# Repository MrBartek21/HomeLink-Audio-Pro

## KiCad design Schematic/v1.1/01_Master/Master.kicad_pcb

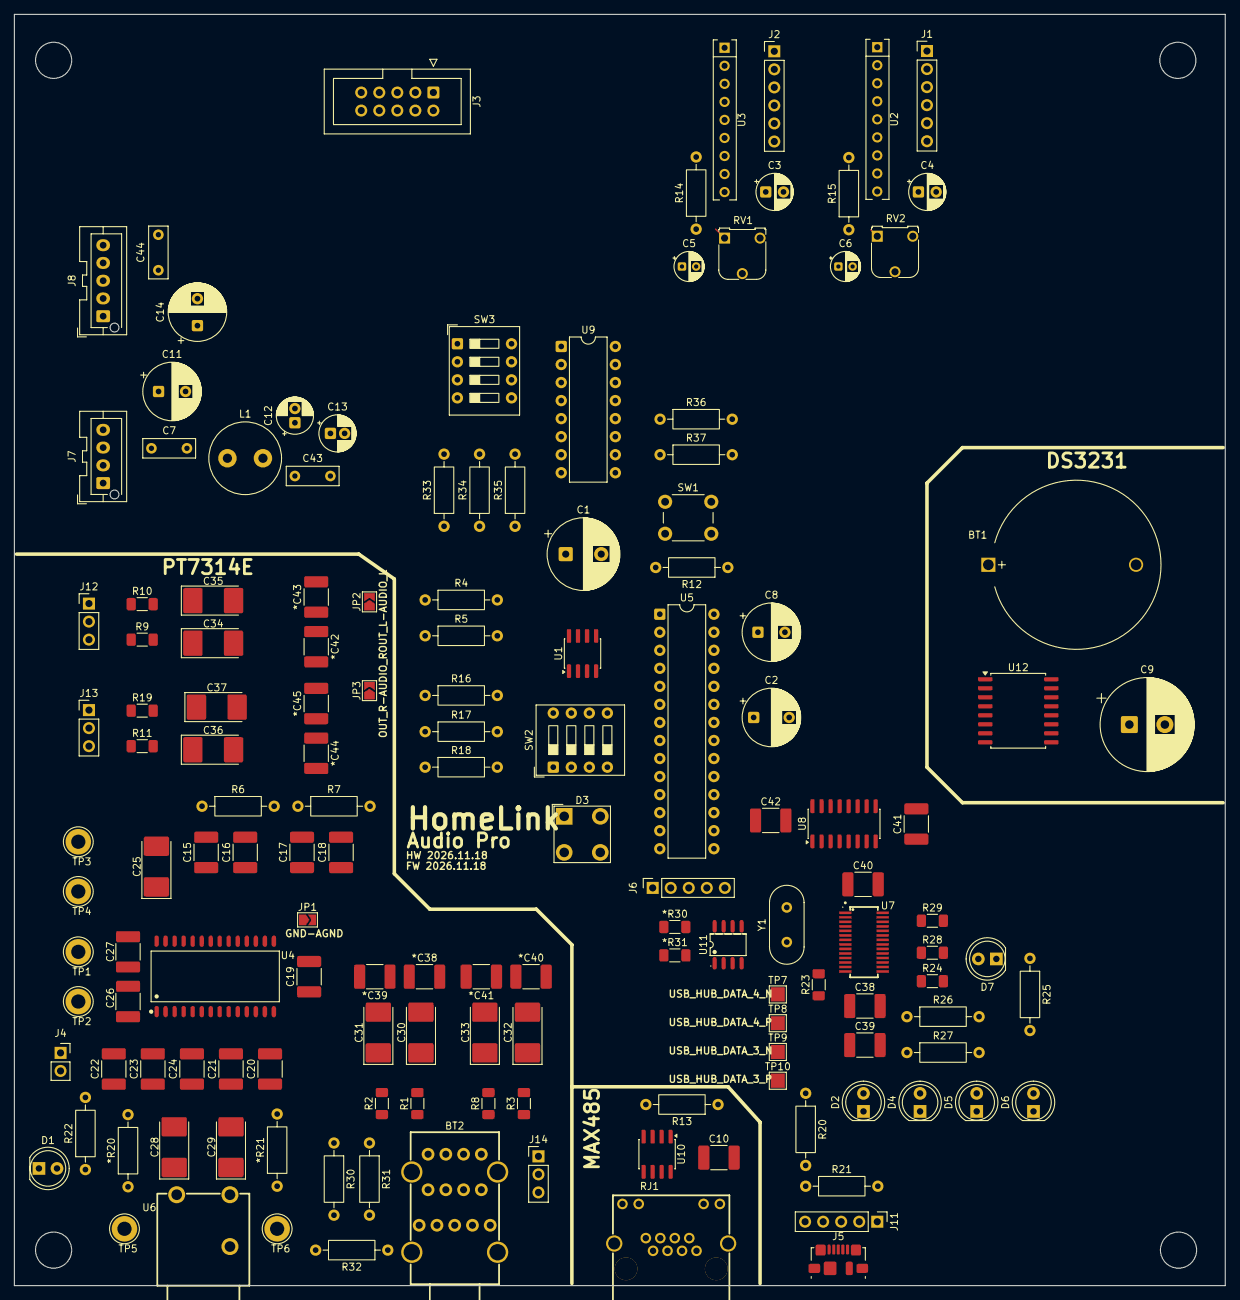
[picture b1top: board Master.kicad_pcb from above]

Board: 2 copper layers, 170.5 x 179.0 mm, 147 parts (0 on the bottom side), 125 nets.

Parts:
*C38, *C39, *C40, *C41, *C42, *C43, *C44, *C45: 470pF; C_1812_4532Metric_Pad1.57x3.40mm_HandSolder
*R20, *R21: 75K; R_Axial_DIN0207_L6.3mm_D2.5mm_P10.16mm_Horizontal
*R30, *R31: 5.1K; R_1206_3216Metric_Pad1.30x1.75mm_HandSolder
BT1: Battery; BatteryHolder_MYOUNG_BS-07-A1BJ001_CR2032
BT2: ABA-JAK-027-K11; AUDIO-TH_ABA-JAK-027-K11
C1: 6.3v 3300uF; CP_Radial_D10.0mm_P5.00mm
C2: 6.3V 1800uF; CP_Radial_D8.0mm_P5.00mm
C3, C4: 16V 10uF; CP_Radial_D5.0mm_P2.50mm
C5, C6: 16V 2.2uF; CP_Radial_D4.0mm_P2.00mm
C7, C43, C44: 100nF 100V; C_Rect_L7.2mm_W2.5mm_P5.00mm
C8: 6.3V 220uF; CP_Radial_D8.0mm_P3.80mm
C9: 35v 1000uF; CP_Radial_D13.0mm_P5.00mm
C10, C15, C16, C17, C18, C20, C21, C26, C39, C40, C41, C42: 100nF; C_1812_4532Metric_Pad1.57x3.40mm_HandSolder
C11, C14: 10V 1000uF; CP_Radial_D8.0mm_P3.80mm
C12: 16V 100uF; CP_Radial_D5.0mm_P2.00mm
C13: 25V 10uF; CP_Radial_D5.0mm_P2.00mm
C19, C22: 2.2uF; C_1812_4532Metric_Pad1.57x3.40mm_HandSolder
C23, C24: 2.7nF; C_1812_4532Metric_Pad1.57x3.40mm_HandSolder
C25: 16V 22uF; CP_EIA-7132-20_AVX-U_HandSolder
C27, C38: 10uF; C_1812_4532Metric_Pad1.57x3.40mm_HandSolder
C28, C29: 16V 10uF; CP_EIA-7132-20_AVX-U_HandSolder
C30, C31, C32, C33, C34, C35, C36, C37: 2.2uF; CP_EIA-7132-20_AVX-U_HandSolder
D1, D2, D4, D5, D6, D7: LED; LED_D5.0mm
D3: LED_Dual_AAKK; LED_BL-FL7680RGB
J1, J2: Conn_01x06_Pin; PinHeader_1x06_P2.54mm_Vertical
J3: IO/I2C; IDC-Header_2x05_P2.54mm_Vertical
J4: 9V_DSP; PinSocket_1x02_P2.54mm_Vertical
J5: USB_B_Micro; USB_Micro-B_Molex_47346-0001
J6: ISP; PinSocket_1x05_P2.54mm_Vertical
J7: POWER; JST_XA_B04B-XASK-1-A_1x04_P2.50mm_Vertical
J8: FrontPanel; JST_XA_B05B-XASK-1-A_1x05_P2.50mm_Vertical
J11: USB; PinHeader_1x05_P2.54mm_Vertical
J12: AUDIO_3; PinHeader_1x03_P2.54mm_Vertical
J13: AUDIO_4; PinHeader_1x03_P2.54mm_Vertical
J14: AUDIO_PORT; PinHeader_1x03_P2.54mm_Vertical
JP1: GND-AGND; SolderJumper-2_P1.3mm_Open_TrianglePad1.0x1.5mm
JP2: OUT_L-AUDIO_L; SolderJumper-2_P1.3mm_Open_TrianglePad1.0x1.5mm
JP3: OUT_R-AUDIO_R; SolderJumper-2_P1.3mm_Open_TrianglePad1.0x1.5mm
L1: 0.16mH / 0.1OHM; L_Radial_D10.0mm_P5.00mm_Fastron_07M
R1, R2, R3, R8, R9, R10, R11, R19: 2.2K; R_1206_3216Metric_Pad1.30x1.75mm_HandSolder
R4, R14, R15: 10K; R_Axial_DIN0207_L6.3mm_D2.5mm_P10.16mm_Horizontal
R5, R12, R13, R21, R30, R31, R32, R33, R36, R37: 5.1K; R_Axial_DIN0207_L6.3mm_D2.5mm_P10.16mm_Horizontal
R6, R7: 5.6K; R_Axial_DIN0207_L6.3mm_D2.5mm_P10.16mm_Horizontal
R16, R17, R18, R20: 1K; R_Axial_DIN0207_L6.3mm_D2.5mm_P10.16mm_Horizontal
R22, R25, R26, R27: 460; R_Axial_DIN0207_L6.3mm_D2.5mm_P10.16mm_Horizontal
R23: 2.7K; R_1206_3216Metric_Pad1.30x1.75mm_HandSolder
R24, R28, R29: 5.1K; R_1206_3216Metric_Pad1.30x1.75mm_HandSolder
R34, R35: 4.7K; R_Axial_DIN0207_L6.3mm_D2.5mm_P10.16mm_Horizontal
RJ1: XY-RJ45R08PC; RJ45-TH_XY-RJ45R08PC
RV1, RV2: 10K; Potentiometer_Runtron_RM-065_Vertical
SW1: SW_Push; SW_PUSH_6mm
SW2, SW3: SW_DIP_x04; SW_DIP_SPSTx04_Slide_9.78x12.34mm_W7.62mm_P2.54mm
TP1: 9V_DSP; TestPoint_Loop_D3.80mm_Drill2.0mm
TP2: GND; TestPoint_Loop_D3.80mm_Drill2.0mm
TP3: SDA; TestPoint_Loop_D3.80mm_Drill2.0mm
TP4: SCL; TestPoint_Loop_D3.80mm_Drill2.0mm
TP5: OUT_L; TestPoint_Loop_D3.80mm_Drill2.0mm
TP6: OUT_R; TestPoint_Loop_D3.80mm_Drill2.0mm
TP7: USB_HUB_DATA_4_N; TestPoint_Pad_2.0x2.0mm
TP8: USB_HUB_DATA_4_P; TestPoint_Pad_2.0x2.0mm
TP9: USB_HUB_DATA_3_N; TestPoint_Pad_2.0x2.0mm
TP10: USB_HUB_DATA_3_P; TestPoint_Pad_2.0x2.0mm
U1: M24C02-FMN; SOIC-8_3.9x4.9mm_P1.27mm
U2, U3: KA2284; SIP-9_22.3x3mm_P2.54mm
U4: PT7314E; SOP-28_L17.9-W7.5-P1.27-LS10.3-BL
U5: ATmega328-P; DIP-28_W7.62mm
U6: AUDIO_OUT; RCA-TH_CAX-AV-213-WR-BK-PHP
U7: FE1.1S; SSOP-28_L9.9-W3.9-P0.635-LS6.0-BL-1
U8: CH340C; SOIC-16_3.9x9.9mm_P1.27mm
U9: PCF8574AP; DIP-16_W7.62mm
U10: MAX485E; SOIC-8_3.9x4.9mm_P1.27mm
U11: 24C02CT/SN_C2061394; SOIC-8_L4.9-W3.9-P1.27-LS6.0-BL
U12: DS3231M; SOIC-16W_7.5x10.3mm_P1.27mm
Y1: 12MHZ; Crystal_HC49-U_Vertical

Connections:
+5V: C1.1, C2.1, C8.1, C9.1, C10.1, C12.1, C13.1, C40.1, C43.1, J1.6, J2.6, L1.2, R4.2, R14.1, R30.2, R31.2, R32.2, R34.1, R35.1, R36.2, RV1.1, SW2.1, SW2.2, SW2.3, SW2.4, SW3.1, SW3.2, SW3.3, SW3.4, U1.8 (VCC), U2.9 (VCC), U3.9 (VCC), U5.7 (VCC), U5.20 (AVCC), U7.20 (VDD5), U8.16 (VCC), U9.16 (VDD), U10.8 (VCC), U12.2 (VCC)
+5V_IN: C7.1, C11.1, J7.2, L1.1
+9V_DSP: C26.1, C27.1, J4.2, R22.2, TP1.1 (1_1), U4.1 (VDD)
/DSP/LIN_1: C30.1, U4.16 (LIN1)
/DSP/LIN_2: C32.1, U4.15 (LIN2)
/DSP/LIN_3: C34.1, U4.14 (LIN3)
/DSP/LIN_4: C36.1, U4.13 (LIN4)
/DSP/RIN_1: C31.1, U4.11 (RIN1)
/DSP/RIN_2: C33.1, U4.10 (RIN2)
/DSP/RIN_3: C35.1, U4.9 (RIN3)
/DSP/RIN_4: C37.1, U4.8 (RIN4)
/Master/MISO: J6.4, U5.18 (PB4)
/Master/MOSI: J6.3, U5.17 (PB3)
/Master/SCK: J6.5, U5.19 (PB5)
/USB/+3V3_FE: *R30.1, *R31.1, C38.1, C39.1, R24.2, R28.2, R29.2, U7.21 (VD33F), U11.8 (VCC)
/USB/DRV: D2.1 (K), D4.2 (A), D5.2 (A), D6.1 (K), D7.2 (A), U7.22 (DRV)
/USB/LED1: *R30.2, R26.1, U7.23 (LED1), U11.6 (SCL)
/USB/LED2: R27.1, U7.24 (LED2)
/USB/TESTJ: *R31.2, U7.27 (TESTJ), U11.5 (SDA)
ACS: J3.6, U5.23 (PC0)
ACTIVITY_ATMEGA8: D3.1 (A1), J3.8
ACTIVITY_ATMEGA328: D3.2 (A2), U5.6 (PD4)
AGND: *C38.1, *C39.1, *C40.1, *C41.1, *C42.1, *C43.1, *C44.1, *C45.1, *R20.2, *R21.2, BT2.1, BT2.4, BT2.6 (SHELL), BT2.24, BT2.34 (24), C20.1, C21.1, C23.1, C24.1, C25.2, J12.2, J13.2, J14.2, JP1.1 (A), R6.2, R7.2, U4.2 (AGND), U6.1
AUDIO_L: C6.2, JP2.2 (B)
AUDIO_R: C5.2, JP3.2 (B)
A_L_1: BT2.22, R1.1
A_L_2: BT2.2, R3.1
A_L_3: J12.3, R9.1
A_L_4: J13.3, R11.1
A_R_1: BT2.25, R2.1
A_R_2: BT2.5, R8.1
A_R_3: J12.1, R10.1
A_R_4: J13.1, R19.1
BTN: J8.1, R36.1, U9.7 (P3)
DE_RE: R13.2, U5.14 (PB0), U10.2 (~RE), U10.3 (DE)
GND: BT1.2 (-), C1.2, C2.2, C3.2, C4.2, C7.2, C8.2, C9.2, C10.2, C11.2, C12.2, C13.2, C14.2, C26.2, C27.2, C38.2, C39.2, C40.2, C41.2, C43.2, C44.2, D1.1 (K), D3.3 (K1), D3.4 (K2), J3.1, J3.10, J4.1, J5.5 (GND), J5.SH (Shield), J6.1, J7.3, J7.4, J8.5, J11.1, JP1.2 (B), R5.1, R12.1, R13.1, R15.1, R16.1, R17.1, R18.1, R21.2, R23.1, R25.2, R33.1, R37.2, RJ1.2, RJ1.10 (L-), RJ1.12 (R-), RJ1.13 (S), RJ1.14 (S), RV2.1, SW1.2, TP2.1 (1_1), U1.4 (VSS), U2.5 (GND), U3.5 (GND), U4.25 (DGND), U5.8 (GND), U5.22 (GND), U7.1 (VSS), U8.1 (GND), U8.15 (R232), U9.8 (GND), U10.5 (GND), U11.1 (A0), U11.2 (A1), U11.3 (A2), U11.4 (VSS), U11.7 (WP), U12.5 (GND), U12.6 (GND), U12.7 (GND), U12.8 (GND), U12.9 (GND), U12.10 (GND), U12.11 (GND), U12.12 (GND), U12.13 (GND)
JACK1_DET: BT2.3, R31.1, U9.4 (P0)
JACK2_DET: BT2.23, R30.1, U9.5 (P1)
JACK3_DET: BT2.33 (23), R32.1, U9.6 (P2)
MASTER_RESET: C42.2, J6.2, R4.1, SW1.1, U5.1 (~RESET/PC6)
unnamed: *C38.2, C30.2, R1.2
unnamed: *C39.2, C31.2, R2.2
unnamed: *C40.2, C32.2, R3.2
unnamed: *C41.2, C33.2, R8.2
unnamed: *C42.2, C34.2, R9.2
unnamed: *C43.2, C35.2, R10.2
unnamed: *C44.2, C36.2, R11.2
unnamed: *C45.2, C37.2, R19.2
unnamed: BT1.1 (+), U12.14 (VBAT)
unnamed: C5.1, RV1.3
unnamed: C6.1, RV2.3
unnamed: C15.2, C16.2, R6.1
unnamed: C17.2, C18.2, R7.1
unnamed: D1.2 (A), R22.1
unnamed: D2.2 (A), D4.1 (K), R26.2
unnamed: D5.1 (K), D6.2 (A), R27.2
unnamed: D7.1 (K), R25.1
unnamed: J1.1, U2.1 (D1)
unnamed: J1.2, U2.2 (D2)
unnamed: J1.3, U2.3 (D3)
unnamed: J1.4, U2.4 (D4)
unnamed: J1.5, U2.6 (D5)
unnamed: J2.1, U3.1 (D1)
unnamed: J2.2, U3.2 (D2)
unnamed: J2.3, U3.3 (D3)
unnamed: J2.4, U3.4 (D4)
unnamed: J2.5, U3.6 (D5)
unnamed: C14.1, C44.1, J7.1, J8.4
unnamed: J5.4 (ID), J11.2
unnamed: BT2.32 (22), J14.1
unnamed: BT2.35 (25), J14.3
unnamed: R16.2, SW2.8, U1.1 (E0)
unnamed: R17.2, SW2.7, U1.2 (E1)
unnamed: R18.2, SW2.6, U1.3 (E2)
unnamed: RV1.2, U2.8 (INPUT)
unnamed: C3.1, R14.2, U2.7 (OUT)
unnamed: RV2.2, U3.8 (INPUT)
unnamed: C4.1, R15.2, U3.7 (OUT)
unnamed: C18.1, U4.19 (BIN_L)
unnamed: C16.1, U4.21 (BIN_R)
unnamed: C17.1, U4.20 (BOUT_L)
unnamed: C15.1, U4.22 (BOUT_R)
unnamed: C19.2, U4.17 (LIN)
unnamed: C20.2, U4.12 (LOUD_L)
unnamed: C21.2, U4.7 (LOUD_R)
unnamed: C19.1, U4.18 (LOUT)
unnamed: C25.1, U4.28 (REF)
unnamed: C22.2, U4.5 (RIN)
unnamed: C22.1, U4.6 (ROUT)
unnamed: C23.2, U4.3 (TREB_L)
unnamed: C24.2, U4.4 (TREB_R)
unnamed: R28.1, U7.19 (BUSJ)
unnamed: TP9.1 (1_1), U7.6 (DM3)
unnamed: TP7.1 (1_1), U7.4 (DM4)
unnamed: TP10.1 (1_1), U7.7 (DP3)
unnamed: TP8.1 (1_1), U7.5 (DP4)
unnamed: R29.1, U7.26 (OVCJ)
unnamed: R23.2, U7.14 (REXT)
unnamed: U7.3 (XIN), Y1.1
unnamed: U7.2 (XOUT), Y1.2
unnamed: R24.1, U7.17 (XRSTJ)
unnamed: C41.1, U8.4 (V3)
unnamed: C42.1, U8.13 (~DTR)
unnamed: R5.2, SW3.8, U9.1 (A0)
unnamed: R12.2, SW3.7, U9.2 (A1)
unnamed: R33.2, SW3.6, U9.3 (A2)
OUT_L: *R20.1, C28.1, C28.2, JP2.1 (A), TP5.1 (1_1), U4.24 (OUT_L), U6.2
OUT_R: *R21.1, C29.1, C29.2, JP3.1 (A), TP6.1 (1_1), U4.23 (OUT_R), U6.3
RJ_LED_ACT: RJ1.11 (R+), U5.11 (PD5)
RJ_LED_LINK: RJ1.9 (L+), U5.12 (PD6)
RS485-A-P: RJ1.3, U10.6 (A)
RS485-B-N: RJ1.4, U10.7 (B)
RX: U5.2 (PD0), U8.3 (RXD)
RX_RS485: U5.4 (PD2), U10.1 (RO)
SCL: J3.4, J8.2, R35.2, TP4.1 (1_1), U1.6 (SCL), U4.27 (SCL), U5.28 (PC5), U9.14 (SCL), U12.16 (SCL)
SDA: J3.2, J8.3, R34.2, TP3.1 (1_1), U1.5 (SDA), U4.26 (SDA), U5.27 (PC4), U9.15 (SDA), U12.15 (SDA)
TX: U5.3 (PD1), U8.2 (TXD)
TX-RS485: U5.5 (PD3), U10.4 (DI)
USB_HOST_5V: J5.1 (VBUS), J11.5, R20.2, R21.1, U7.18 (VBUSM)
USB_HOST_DATA_N: J5.2 (D-), J11.4, U7.15 (DMU)
USB_HOST_DATA_P: J5.3 (D+), J11.3, U7.16 (DPU)
USB_HOST_DET: R20.1, R37.1, U9.9 (P4)
USB_HUB_DATA_1_N: U7.10 (DM1), U8.6 (UD-)
USB_HUB_DATA_1_P: U7.11 (DP1), U8.5 (UD+)
W_Prot: U1.7 (~WC), U5.15 (PB1)

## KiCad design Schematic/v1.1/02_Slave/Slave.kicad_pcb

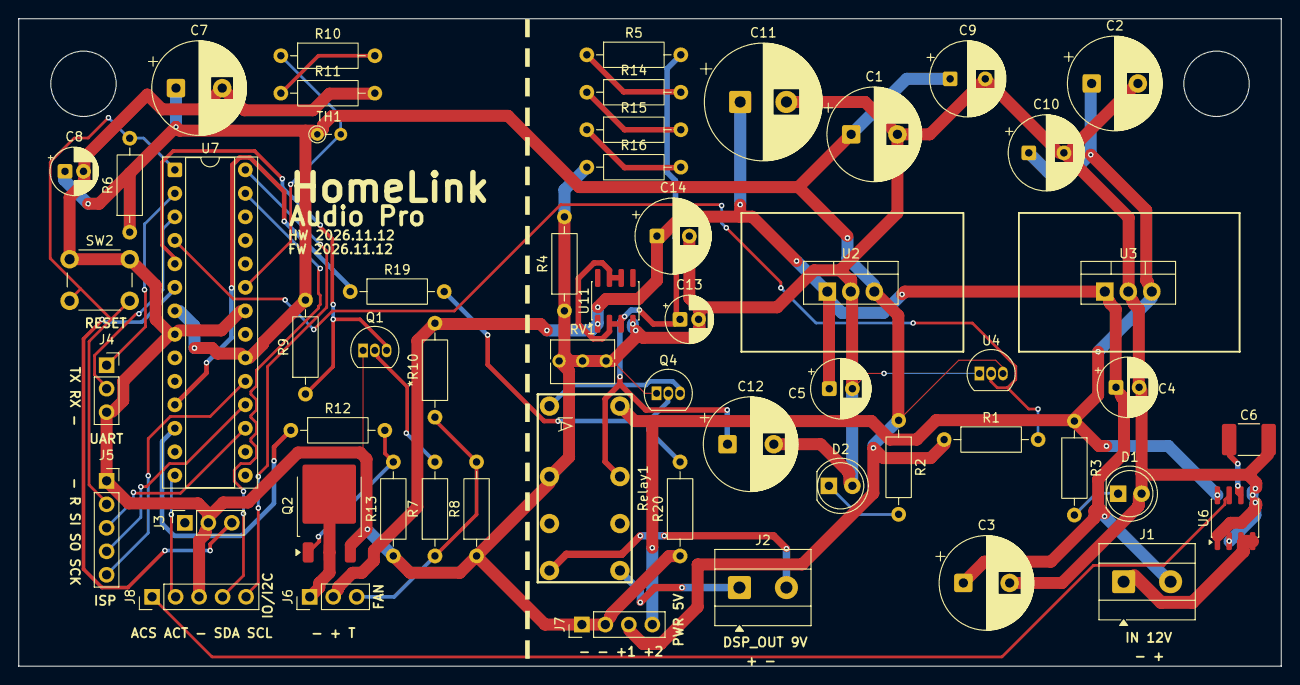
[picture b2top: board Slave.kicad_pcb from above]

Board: 2 copper layers, 136.5 x 70.0 mm, 56 parts (0 on the bottom side), 37 nets.

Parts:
*R10: *5.1K; R_Axial_DIN0207_L6.3mm_D2.5mm_P10.16mm_Horizontal
C1, C2: 6.3V 3300uF; CP_Radial_D10.0mm_P5.00mm
C3: 16v 1000uF; CP_Radial_D10.0mm_P5.00mm
C4, C5: 35v 100uF; CP_Radial_D6.3mm_P2.50mm
C6: 1nF; C_1812_4532Metric_Pad1.57x3.40mm_HandSolder
C7: 6.3v 1500uF; CP_Radial_D10.0mm_P5.00mm
C8: 16v 100uF; CP_Radial_D5.0mm_P2.00mm
C9, C10: 6.3V 1800uF; CP_Radial_D8.0mm_P3.80mm
C11: 25V 1000uF; CP_Radial_D12.5mm_P5.00mm
C12: 16V 1500uF; CP_Radial_D10.0mm_P5.00mm
C13: 16V 22uF; CP_Radial_D5.0mm_P2.00mm
C14: 450V 4.7uF; CP_Radial_D8.0mm_P3.50mm
D1, D2: LED; LED_D5.0mm
J1: 12V_IN; TerminalBlock_MetzConnect_Type101_RT01602HBWC_1x02_P5.08mm_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
J2: DSP_OUT; TerminalBlock_MetzConnect_Type101_RT01602HBWC_1x02_P5.08mm_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
J3: TACHO; PinSocket_1x03_P2.54mm_Vertical
J4: UART; PinSocket_1x03_P2.54mm_Vertical
J5: ISP; PinSocket_1x05_P2.54mm_Vertical
J6: FAN; PinHeader_1x03_P2.54mm_Vertical
J7: POWER; PinHeader_1x04_P2.54mm_Vertical
J8: IO/I2C; PinHeader_1x05_P2.54mm_Vertical
Q1, Q4: 2N3904; TO-92_Inline
Q2: Q_NMOS_GDS; TO-252-3_TabPin2
R1, R2, R3, R12, R19: 1K; R_Axial_DIN0207_L6.3mm_D2.5mm_P10.16mm_Horizontal
R4: 1.75K; R_Axial_DIN0207_L6.3mm_D2.5mm_P10.16mm_Horizontal
R5: 200; R_Axial_DIN0207_L6.3mm_D2.5mm_P10.16mm_Horizontal
R6: 10K; R_Axial_DIN0207_L6.3mm_D2.5mm_P10.16mm_Horizontal
R7, R10, R11, R13, R20: 5.1K; R_Axial_DIN0207_L6.3mm_D2.5mm_P10.16mm_Horizontal
R8, R9: 4.7K; R_Axial_DIN0207_L6.3mm_D2.5mm_P10.16mm_Horizontal
R14, R15, R16: 15; R_Axial_DIN0207_L6.3mm_D2.5mm_P10.16mm_Horizontal
RV1: 20K; Potentiometer_Bourns_3266Y_Vertical
Relay1: HFD27/005-S; RELAY-TH_HFD27-005-S
SW2: RESET; SW_PUSH_6mm
TH1: Thermistor_NTC; R_Axial_DIN0204_L3.6mm_D1.6mm_P2.54mm_Vertical
U2, U3: L7805; TO-220-3_Vertical
U4: DS18B20; TO-92_Inline
U6: ACS712xLCTR-30A; SOIC-8_3.9x4.9mm_P1.27mm
U7: ATmega8-16P; DIP-28_W7.62mm_Socket
U11: LM317L_SO8; SOIC-8_3.9x4.9mm_P1.27mm

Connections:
+5V: C1.1, C7.1, C8.1, C9.1, J7.3, R1.1, R2.1, R6.1, R9.2, TH1.1, U2.3 (OUT), U4.3 (V_{DD}), U7.7 (VCC), U7.20 (AVCC)
+5V_2: C2.1, C10.1, J7.4, R3.1, Relay1.16, U3.3 (OUT), U6.8 (VCC)
+12V: *R10.2, C3.1, C4.1, C5.1, C11.1, C14.1, J1.2, J6.2, U2.1 (IN), U3.1 (IN), U11.1 (VI)
/Slave/MISO: J5.4, U7.18 (PB4)
/Slave/MOSI: J5.3, U7.17 (PB3)
/Slave/RESET: J5.2, R6.2, SW2.2, U7.1 (PC6/~RESET)
/Slave/RX: J4.2, U7.3 (PD1)
/Slave/SCK: J5.5, U7.19 (PB5)
/Slave/TX: J4.1, U7.2 (PD0)
ACS_OUT: J8.1, U6.7 (VIOUT)
ACTIVITY_OUT: J8.2, U7.14 (PB0)
DQ: R1.2, U4.2 (DQ), U7.4 (PD2)
FAN_M: J6.1, Q2.2 (D)
GND: C1.2, C2.2, C3.2, C4.2, C5.2, C6.2, C7.2, C8.2, C9.2, C10.2, C11.2, C12.2, C13.2, C14.2, D1.2 (A), D2.2 (A), J3.2, J4.3, J5.1, J7.1, J7.2, J8.3, Q1.1 (E), Q2.3 (S), Q4.1 (E), R4.1, R4.2, R8.1, R11.2, R13.1, R16.1, R20.1, RV1.1, RV1.2, RV1.3, Relay1.4, SW2.1, U2.2 (GND), U3.2 (GND), U4.1 (GND), U6.1 (IP+), U6.2 (IP+), U6.5 (GND), U7.8 (GND), U7.22 (AGND), U11.4 (ADJ)
NTC: R10.1, TH1.2, U7.23 (PC0)
unnamed: C12.1, C13.1, R5.2, Relay1.13, U11.2 (VO), U11.3 (VO), U11.6 (VO), U11.7 (VO)
unnamed: D1.1 (K), R3.2
unnamed: D2.1 (K), R2.2
unnamed: J1.1, U6.3 (IP-), U6.4 (IP-)
unnamed: J2.1, Relay1.9
unnamed: J2.2, Relay1.8
unnamed: J3.3, U7.6 (PD4)
unnamed: Q1.2 (B), R7.2
unnamed: Q2.1 (G), R12.2, R13.2
unnamed: Q4.2 (B), R19.2, R20.2
unnamed: Q4.3 (C), Relay1.1
unnamed: R10.2, R11.1
unnamed: R14.1, R15.2
unnamed: R5.1, R14.2
unnamed: R15.1, R16.2
unnamed: C6.1, U6.6 (FILTER)
RLY1: R19.1, U7.11 (PD5)
RLY2: R12.1, U7.12 (PD6)
SCL_OUT: J8.5, U7.28 (PC5)
SDA_OUT: J8.4, U7.27 (PC4)
TACHO: Q1.3 (C), R9.1, U7.5 (PD3)
TACHO_FAN: *R10.1, J6.3, R7.1, R8.2

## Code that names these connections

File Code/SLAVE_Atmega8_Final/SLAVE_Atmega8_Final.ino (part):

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#include <math.h>

// HomeLink Audio Pro - ATmega8 final slave
// PC0 NTC, PC4/PC5 I2C slave, PD2 DS18B20, PD5 RLY1, PD6 RLY2, PB0 LED.
// PD0/PD1 are diagnostic UART at 9600 baud. No external crystal.

#define I2C_ADDRESS          0x12
#define DS18B20_BIT          PD2
#define TACHO_BIT            PD3
#define TACHO_MODE_BIT       PD4
#define RELAY1_BIT           PD5
#define RELAY2_BIT           PD6
#define ACTIVITY_LED_BIT     PB0
#define RELAY_ACTIVE_LOW     1

// Divider: +5V -> NTC -> PC0 -> 10k -> GND.
#define NTC_FIXED_OHMS       10000.0f
#define NTC_NOMINAL_OHMS     47000.0f
#define NTC_NOMINAL_C        25.0f
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
static uint16_t readAdc0()
{
    ADMUX = _BV(REFS0); // AVCC reference, ADC0/PC0
    ADCSRA = _BV(ADEN) | _BV(ADPS2) | _BV(ADPS1) | _BV(ADPS0);
    delayMicroseconds(100);
    ADCSRA |= _BV(ADSC);
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    Wire.onRequest(onRequest);

    tachoEnabled = (PIND & _BV(TACHO_MODE_BIT)) == 0;
    // INT1 / PD3, falling edge. The transistor output is pulled up to +5 V.
    // ATmega8 uses MCUCR/GICR, unlike newer AVR devices using EICRA/EIMSK.
    MCUCR = (MCUCR & (uint8_t)~(_BV(ISC11) | _BV(ISC10))) | _BV(ISC11);
    GICR |= _BV(INT1);
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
